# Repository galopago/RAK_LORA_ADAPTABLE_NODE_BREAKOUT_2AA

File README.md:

# RAK_LORA_ADAPTABLE_NODE_BREAKOUT_2AA

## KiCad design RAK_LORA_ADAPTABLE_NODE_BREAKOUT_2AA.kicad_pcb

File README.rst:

=======================================================================================================================================
Breakout board for RAK811/RAK4200 LoRa adaptable nodes, small size, used when both AA battery holders were installed.
=======================================================================================================================================

Breakout board & prototype area to mount a few ( and small ) thru-hole components to interface LoRa node. Also can be used as a template for a custom interface board. 

Read this in other languages: `Español </docs/README.es.rst>`_

.. image:: /docs/pcb3d.png

Key features:
-------------
* Double sided traces and pads for added strength
* Prototype area with two parallel tracks connecting multiple pads, to be used as a power&ground rails
* Solder directly to the node's pcb using male header pins for a permanent, rigid  and low height card
* Connect to the node's pcb using male-female pin header combination, for a more flexible solution

How to use this repository
--------------------------
The PCB was developed in KiCad V5.1,

Directory structure
-------------------
* The root folder contains KiCad files: project, schematic and PCB.
* gerber/single directory contains ready to manufacture files, for a single board.
* gerber/panel_100mmx100mm directory contains ready to manufacture files that fits in a 100mm x 100mm panel (use Vcuts!).

License
-------

.. image:: https://i.creativecommons.org/l/by/4.0/88x31.png
   :target: http://creativecommons.org/licenses/by/4.0/

This is an Open Hardware project and is licensed under a `Creative Commons Attribution 4.0 International License, <http://creativecommons.org/licenses/by/4.0/>`_

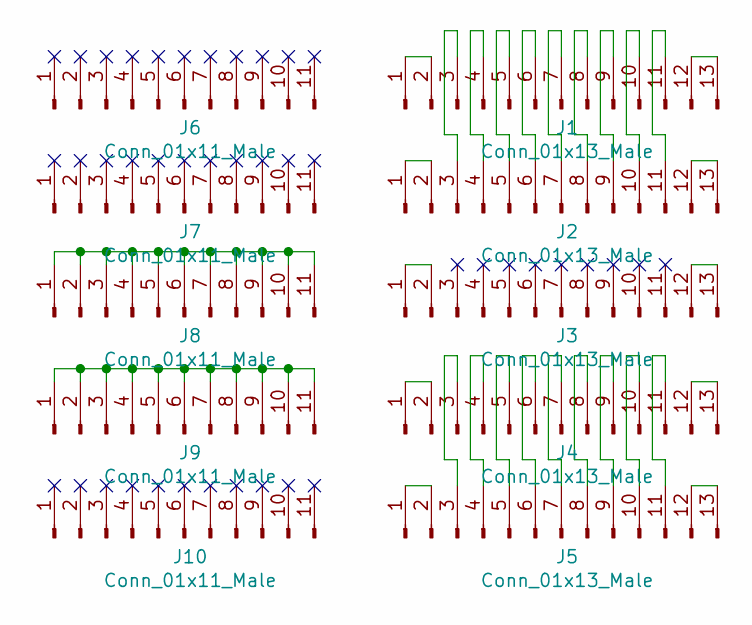
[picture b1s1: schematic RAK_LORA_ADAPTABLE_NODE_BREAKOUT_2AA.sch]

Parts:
J1, J2, J3, J4, J5: Conn_01x13_Male; PinHeader_1x13_P2.54mm_Vertical
J6, J7, J8, J9, J10: Conn_01x11_Male; PinHeader_1x11_P2.54mm_Vertical

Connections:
unnamed: J1.1, J1.2
unnamed: J1.3, J2.3
unnamed: J1.4, J2.4
unnamed: J1.5, J2.5
unnamed: J1.6, J2.6
unnamed: J1.7, J2.7
unnamed: J1.8, J2.8
unnamed: J1.9, J2.9
unnamed: J1.10, J2.10
unnamed: J1.11, J2.11
unnamed: J1.12, J1.13
unnamed: J2.1, J2.2
unnamed: J2.12, J2.13
unnamed: J3.1, J3.2
unnamed: J3.12, J3.13
unnamed: J4.1, J4.2
unnamed: J4.3, J5.3
unnamed: J4.4, J5.4
unnamed: J4.5, J5.5
unnamed: J4.6, J5.6
unnamed: J4.7, J5.7
unnamed: J4.8, J5.8
unnamed: J4.9, J5.9
unnamed: J4.10, J5.10
unnamed: J4.11, J5.11
unnamed: J4.12, J4.13
unnamed: J5.1, J5.2
unnamed: J5.12, J5.13
unnamed: J8.1, J8.2, J8.3, J8.4, J8.5, J8.6, J8.7, J8.8, J8.9, J8.10, J8.11
unnamed: J9.1, J9.2, J9.3, J9.4, J9.5, J9.6, J9.7, J9.8, J9.9, J9.10, J9.11

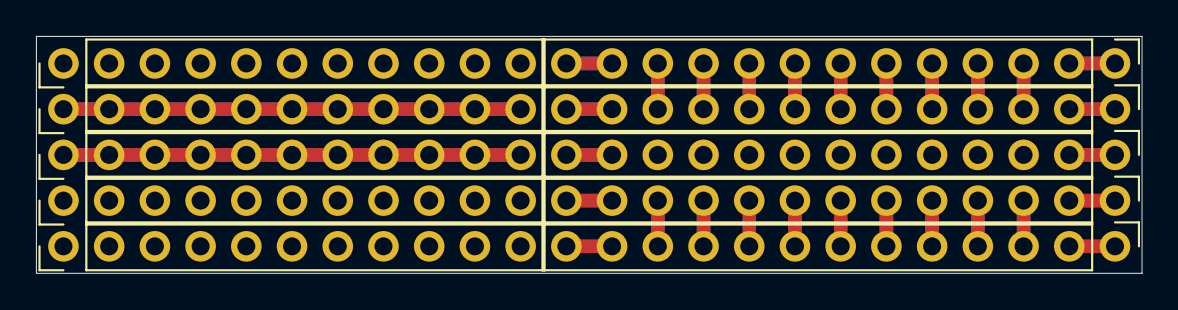
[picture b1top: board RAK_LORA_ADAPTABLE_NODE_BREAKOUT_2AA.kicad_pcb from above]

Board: 2 copper layers, 61.4 x 13.2 mm, 10 parts (0 on the bottom side), 30 nets.

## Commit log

2020-08-06 schematic, pbg and gerbers
2020-08-08 readme file started, needs care
2020-08-09 redme finished, need some corrections
2020-08-10 English readme finished
2020-08-10 Spanish readme started
2020-08-10 Spanish readme corrections
2020-08-10 license file
2020-10-11 pcb pinout layout
2020-10-11 delted svg source files
